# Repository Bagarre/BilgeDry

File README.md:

# BilgeDry Production Refactor

This version is a real step closer to the alternator project style rather than a simple cleanup.

## What changed

- Reworked the pump logic into a non-blocking cycle controller with explicit states:
  - `Idle`
  - `Prime`
  - `Running`
  - `Settling`
  - `Complete`
  - `Fault`
- Split responsibilities into focused modules:
  - `Storage` for persistent config
  - `LogManager` for structured event logging
  - `SensorManager` for INA260 handling and unit normalization
  - `NetworkManager` for STA/AP/mDNS/time sync
  - `CycleController` for zone sequencing and decision logic
  - `WebServerManager` for a cleaner REST API
- Replaced the old flat UI field sprawl with a cleaner JSON contract built around arrays and grouped config.
- Added cycle fault tracking, abort handling, queueable manual runs, and explicit per-zone results.
- Added version/build metadata to the API.
- Moved web assets under `/assets` and structured the frontend into API/state/render/main files.

## Why this is better

The original project worked like a single long script. That is fine until you want to add retries, diagnostics, better status, richer logs, NMEA integration, or a more capable UI. Then it becomes a mess fast.

This version is shaped so those next steps are practical.

## Important behavior notes

- INA260 current is treated as **amps**, converted from the library's **mA** reading.
- A zone is considered to have seen water once current reaches `wetCurrentA` during the run.
- A zone is considered dry once current drops below `dryCurrentA`.
- A fault is raised if current reaches `faultCurrentA`.
- The controller no longer blocks the whole app with multi-second `delay()` calls during a cycle.

## Current API surface

- `GET /api/v1/status`
- `GET /api/v1/config`
- `POST /api/v1/config`
- `GET /api/v1/network`
- `POST /api/v1/network`
- `POST /api/v1/control/run`
- `POST /api/v1/control/abort`
- `POST /api/v1/control/enable`
- `GET /api/v1/logs`
- `POST /api/v1/logs/clear`
- `POST /api/v1/reboot`

## Project structure

```text
BilgeDry_production/
├── README.md
└── esp32/main/
    ├── main.ino
    ├── BilgeDryApp.cpp/.h
    ├── AppTypes.h
    ├── AppVersion.h
    ├── Defaults.h
    ├── Pins.h
    ├── Storage.cpp/.h
    ├── LogManager.cpp/.h
    ├── SensorManager.cpp/.h
    ├── NetworkManager.cpp/.h
    ├── CycleController.cpp/.h
    ├── WebServerManager.cpp/.h
    └── data/
        ├── index.html
        └── assets/
            ├── styles.css
            ├── api.js
            ├── state.js
            ├── render.js
            └── main.js
```

## What still needs real hardware validation

This is the honest part:

- It is structurally much better, but I did not compile and flash it on your exact board here.
- Threshold values will still need tuning on your actual pump and plumbing.
- The current-based wet/dry model is only as good as the pump signature in the real boat.
- If the solenoid timing needs per-zone customization, that is not added yet.
- There is no EEPROM wear strategy beyond normal SPIFFS file saves.

## Best next improvements

1. Add per-zone calibration values instead of one global wet/dry threshold.
2. Add startup self-test and sensor health reporting to status.
3. Add retry logic for suspicious short runs.
4. Add a lightweight event history / metrics page.
5. Add optional NMEA 2000 publish-only status later if you want it to match the rest of the boat systems.

## Recommendation

This is in a good place to become the one you build and share first. It is much easier to reason about, safer to extend, and closer to how the alternator project should feel across the whole codebase.

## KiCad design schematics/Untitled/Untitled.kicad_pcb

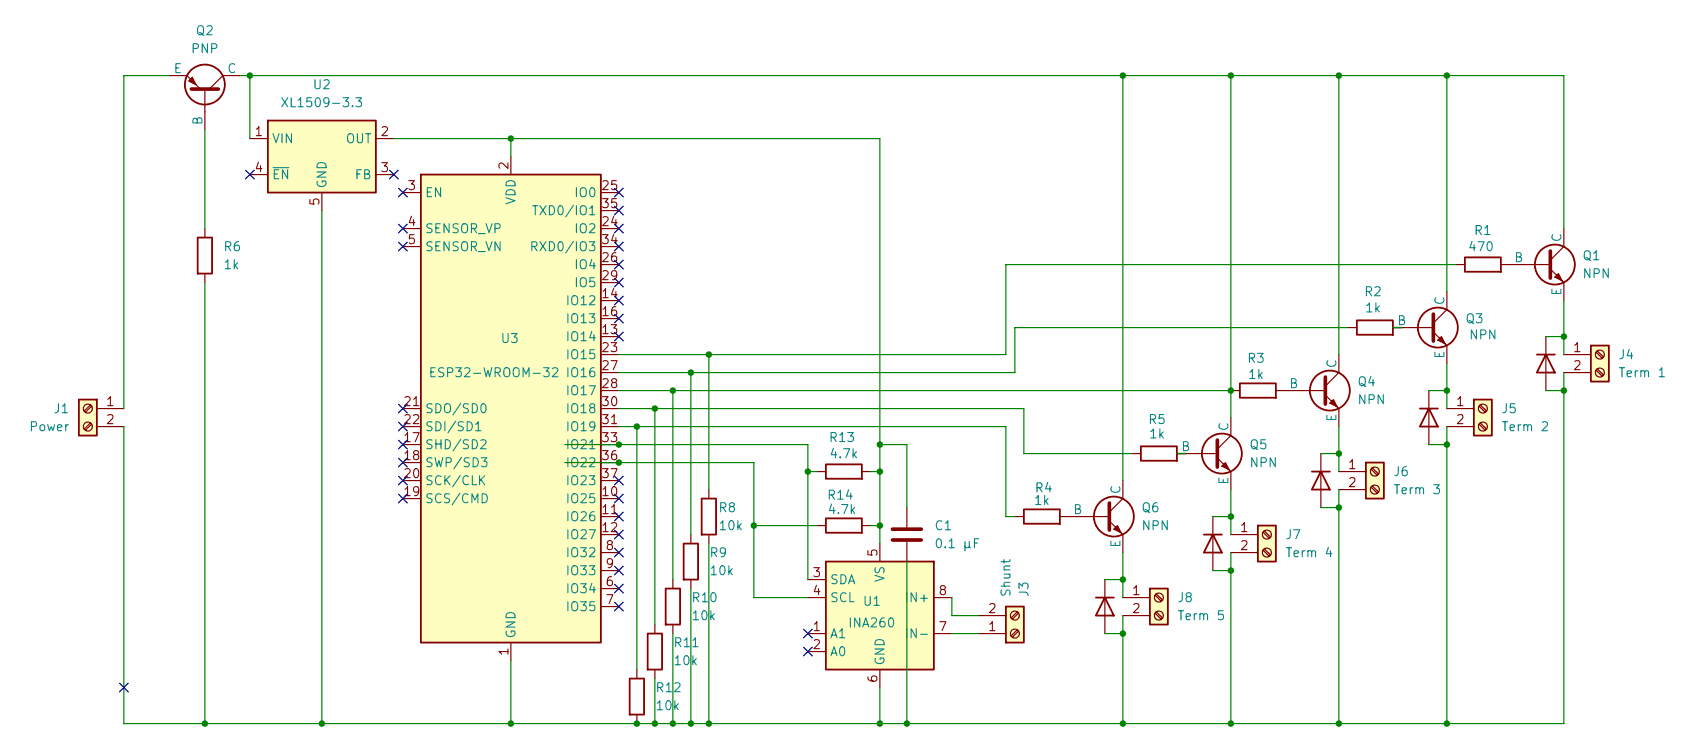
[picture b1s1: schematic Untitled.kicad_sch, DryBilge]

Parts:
C1: 0.1 µF; R_Axial_DIN0207_L6.3mm_D2.5mm_P7.62mm_Horizontal
D1, D2, D3, D4, D5: D; R_Axial_DIN0207_L6.3mm_D2.5mm_P7.62mm_Horizontal
J1: Power; TerminalBlock_Altech_AK300-2_P5.00mm
J3: Shunt; TerminalBlock_Altech_AK300-2_P5.00mm
J4: Term 1; TerminalBlock_Altech_AK300-2_P5.00mm
J5: Term 2; TerminalBlock_Altech_AK300-2_P5.00mm
J6: Term 3; TerminalBlock_Altech_AK300-2_P5.00mm
J7: Term 4; TerminalBlock_Altech_AK300-2_P5.00mm
J8: Term 5; TerminalBlock_Altech_AK300-2_P5.00mm
Q1, Q3, Q4, Q5, Q6: NPN; TO-220-3_Vertical
Q2: PNP; TO-220-3_Vertical
R1: 470; R_Axial_DIN0207_L6.3mm_D2.5mm_P7.62mm_Horizontal
R2, R3, R4, R5, R6: 1k; R_Axial_DIN0207_L6.3mm_D2.5mm_P7.62mm_Horizontal
R8, R9, R10, R11, R12: 10k; R_Axial_DIN0207_L6.3mm_D2.5mm_P7.62mm_Horizontal
R13, R14: 4.7k; R_Axial_DIN0207_L6.3mm_D2.5mm_P7.62mm_Horizontal
U1: INA260; SOIC-8_3.9x4.9mm_P1.27mm
U2: XL1509-3.3; SOIC-8_3.9x4.9mm_P1.27mm
U3: ESP32-WROOM-32

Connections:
unnamed: C1.2, D1.2 (A), D2.2 (A), D3.2 (A), D4.2 (A), D5.2 (A), J1.2, J4.2, J5.2, J6.2, J7.2, J8.2, R6.2, R8.2, R9.2, R10.2, R11.2, R12.2, U1.6 (GND), U2.5 (GND), U2.6 (GND), U2.7 (GND), U2.8 (GND), U3.1 (GND), U3.15 (GND), U3.38 (GND), U3.39 (GND)
unnamed: D1.1 (K), J4.1, Q1.3 (E)
unnamed: D2.1 (K), J5.1, Q3.3 (E)
unnamed: D3.1 (K), J6.1, Q4.3 (E)
unnamed: D4.1 (K), J7.1, Q5.3 (E)
unnamed: D5.1 (K), J8.1, Q6.3 (E)
unnamed: J1.1, Q2.3 (E)
unnamed: J3.1, U1.7 (IN-)
unnamed: J3.2, U1.8 (IN+)
unnamed: Q1.2 (B), R1.2
unnamed: Q1.1 (C), Q2.1 (C), Q3.1 (C), Q4.1 (C), Q5.1 (C), Q6.1 (C), R3.1, R10.1, U2.1 (VIN), U3.28 (IO17)
unnamed: Q2.2 (B), R6.1
unnamed: Q3.2 (B), R2.2
unnamed: Q4.2 (B), R3.2
unnamed: Q5.2 (B), R5.2
unnamed: Q6.2 (B), R4.2
unnamed: R14.1, U1.4 (SCL), U3.36 (IO22)
unnamed: R13.1, U1.3 (SDA), U3.33 (IO21)
unnamed: C1.1, R13.2, R14.2, U1.5 (VS), U2.2 (OUT), U3.2 (VDD)
unnamed: R1.1, R8.1, U3.23 (IO15)
unnamed: R2.1, R9.1, U3.27 (IO16)
unnamed: R5.1, R11.1, U3.30 (IO18)
unnamed: R4.1, R12.1, U3.31 (IO19)

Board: 2 copper layers, 35 parts (0 on the bottom side), 23 nets, no tracks yet.

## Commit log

2025-05-04 First post
    Initial build
2025-05-06 Comments
    Added comments to each file
2025-05-06 Schematic added
2025-05-06 added drawing
2025-05-06 schematic update
2025-05-06 Added r values
2025-05-06 image added
2025-05-06 Update README.md
    Typo
2025-05-06 Update schematic.jpg
    cleaner image
2025-05-06 Upgraded to ESP32
    removed the nmea2k and added wifi. Has status and config web pages
2025-05-06 Remove .DS
2025-05-06 Remove .DS_Store and update .gitignore
2025-05-17 One Big Mess
    Just a lot of updates
2025-05-21 To much to mention
2025-06-22 Cleanup
2026-05-03 reefactor

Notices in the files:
schematics/Untitled/Untitled.kicad_sch:
2025 Bagarre — Licensed under the MIT License
